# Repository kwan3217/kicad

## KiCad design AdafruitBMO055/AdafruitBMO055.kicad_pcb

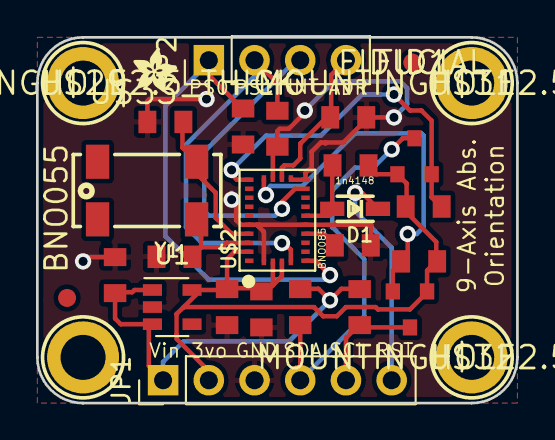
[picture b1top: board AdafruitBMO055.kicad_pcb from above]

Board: 2 copper layers, 26.7 x 20.3 mm, 31 parts (0 on the bottom side), 16 nets.

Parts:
C1, C2: 22pF; SMD_0805
C3, C4: 0.1uF; SMD_0805
C5, C6: 10uF; SMD_0805
D1: 1n4148; SOD-323
FID1, FID2: FIDUCIAL; FIDUCIAL_1MM
JP1: Pin_Header_Straight_1x06_Pitch2.54mm
JP2: Pin_Header_Straight_1x04_Pitch2.54mm
Q1, Q2: BSS138; SOT-23
R3, R4, R5, R6, R7, R8, R9, R10: 10K; SMD_0805
U1: MIC5225; SOT-23-5
U$2: BNO085; BNO055
U$3: PCBFEAT-REV-040
U$28: ADAFRUIT_TEXT_20MM
U$29, U$30, U$31, U$32: MOUNTINGHOLE2.5_THICK; MOUNTINGHOLE_2.5_PLATED_THICK
U$33: ADAFRUIT_2.5MM
Y1: 32.768kHz; CRYSTAL_8X3.8

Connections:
+3V3: C4.2, C6.1, JP1.2, Q1.1, Q2.1, R6.1, R7.1, R10.1, U1.5, U$2.3, U$2.4, U$2.28
+5V: C5.1, JP1.1, R8.1, R9.1, U1.1, U1.3
/I2CADDR_3V: JP2.4, R5.1, U$2.17
/INT_3V: JP2.3, U$2.14
/N$1: C1.2, U$2.27, Y1.1
/N$2: C2.2, U$2.26, Y1.2
/N$3: C3.2, U$2.9
/NRESET_3V: D1.2, R10.2, U$2.11
/PS0_3V: JP2.1, R3.1, U$2.6
/PS1_3V: JP2.2, R4.1, U$2.5
/RST_5V: D1.1, JP1.6
/SCL_3V: Q2.2, R7.2, U$2.19
/SCL_5V: JP1.5, Q2.3, R9.2
/SDA_3V: Q1.2, R6.2, U$2.20
/SDA_5V: JP1.4, Q1.3, R8.2
GND: C1.1, C2.1, C3.1, C4.1, C5.2, C6.2, JP1.3, R3.2, R4.2, R5.2, U1.2, U$2.2, U$2.10, U$2.15, U$2.16, U$2.18, U$2.25

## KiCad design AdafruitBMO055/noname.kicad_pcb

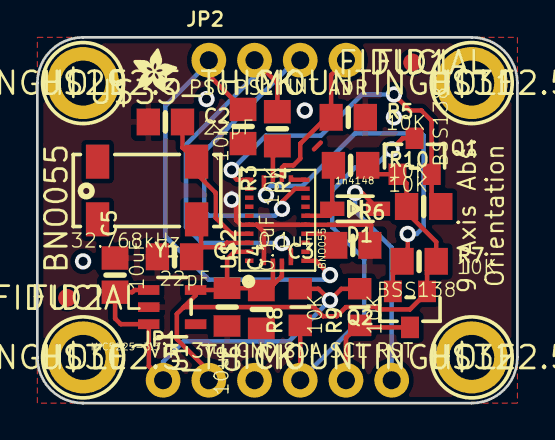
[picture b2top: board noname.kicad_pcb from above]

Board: 2 copper layers, 26.7 x 20.3 mm, 31 parts (0 on the bottom side), 16 nets.

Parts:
C1, C2: 22pF; 0805-NO
C3: 0.1uF; 0805-NO
C4: 0.1uF; 0805_10MGAP
C5: 10uF; 0805-NO
C6: 10uF; 0805_10MGAP
D1: 1n4148; SOD-323
FID1, FID2: FIDUCIAL; FIDUCIAL_1MM
JP1: 1X06_ROUND_76
JP2: 1X04_ROUND_76
Q1, Q2: BSS138; SOT23-WIDE
R3, R4, R5, R6, R7, R10: 10K; 0805-NO
R8, R9: 10K; _0805MP
U1: MIC5225-3.3; SOT23-5
U$2: BNO055
U$3: PCBFEAT-REV-040
U$28: ADAFRUIT_TEXT_20MM
U$29, U$30, U$31, U$32: MOUNTINGHOLE2.5_THICK; MOUNTINGHOLE_2.5_PLATED_THICK
U$33: ADAFRUIT_2.5MM
Y1: 32.768kHz; CRYSTAL_8X3.8

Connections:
3.3V: C4.2, C6.1, JP1.2, Q1.1, Q2.1, R6.2, R7.2, R10.2, U1.5, U$2.3, U$2.4, U$2.28
5.0V: C5.1, JP1.1, R8.2, R9.2, U1.1, U1.3
GND: C1.1, C2.1, C3.1, C4.1, C5.2, C6.2, JP1.3, R3.2, R4.2, R5.2, U1.2, U$2.2, U$2.10, U$2.15, U$2.16, U$2.18, U$2.25
I2CADDR_3V: JP2.4, R5.1, U$2.17
INT_3V: JP2.3, U$2.14
unnamed: C1.2, U$2.27, Y1.P$4
unnamed: C2.2, U$2.26, Y1.P$1
unnamed: C3.2, U$2.9
NRESET_3V: D1.A, R10.1, U$2.11
PS0_3V: JP2.1, R3.1, U$2.6
PS1_3V: JP2.2, R4.1, U$2.5
RST_5V: D1.C, JP1.6
SCL_3V: Q2.2, R7.1, U$2.19
SCL_5V: JP1.5, Q2.3, R9.1
SDA_3V: Q1.2, R6.1, U$2.20
SDA_5V: JP1.4, Q1.3, R8.1

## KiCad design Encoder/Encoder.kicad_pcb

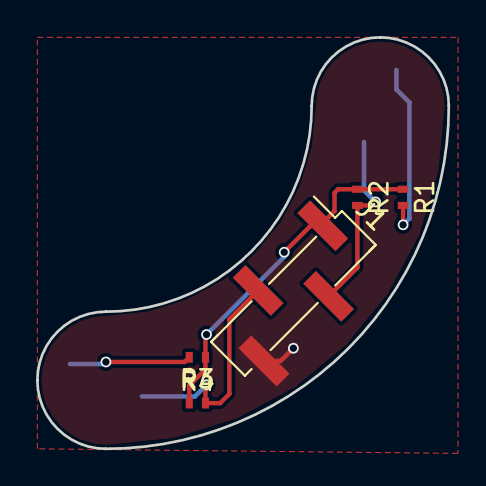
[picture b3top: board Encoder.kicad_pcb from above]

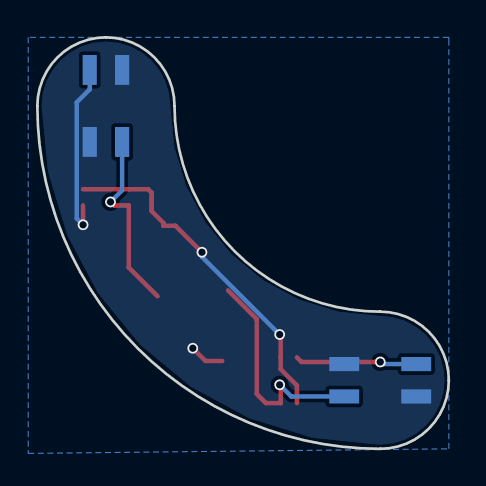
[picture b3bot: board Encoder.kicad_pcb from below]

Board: 2 copper layers, 22.9 x 22.9 mm, 7 parts (2 on the bottom side), 6 nets.

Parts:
J1: CONN_01X04; Pin_Header_Straight_1x04_Pitch2.54mm_SMD_Pin1Left
R1, R3: 220; R_0402_NoSilk
R2, R4: 10k; R_0402_NoSilk
U1, U2: QRE1113

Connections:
/D0: R1.2, U1.1
/D1: R3.2, U2.1
/ENC0: J1.2, R2.2, U1.3
/ENC1: J1.3, R4.2, U2.3
GND: J1.4, U1.2, U1.4, U2.2, U2.4
VCC: J1.1, R1.1, R2.1, R3.1, R4.1

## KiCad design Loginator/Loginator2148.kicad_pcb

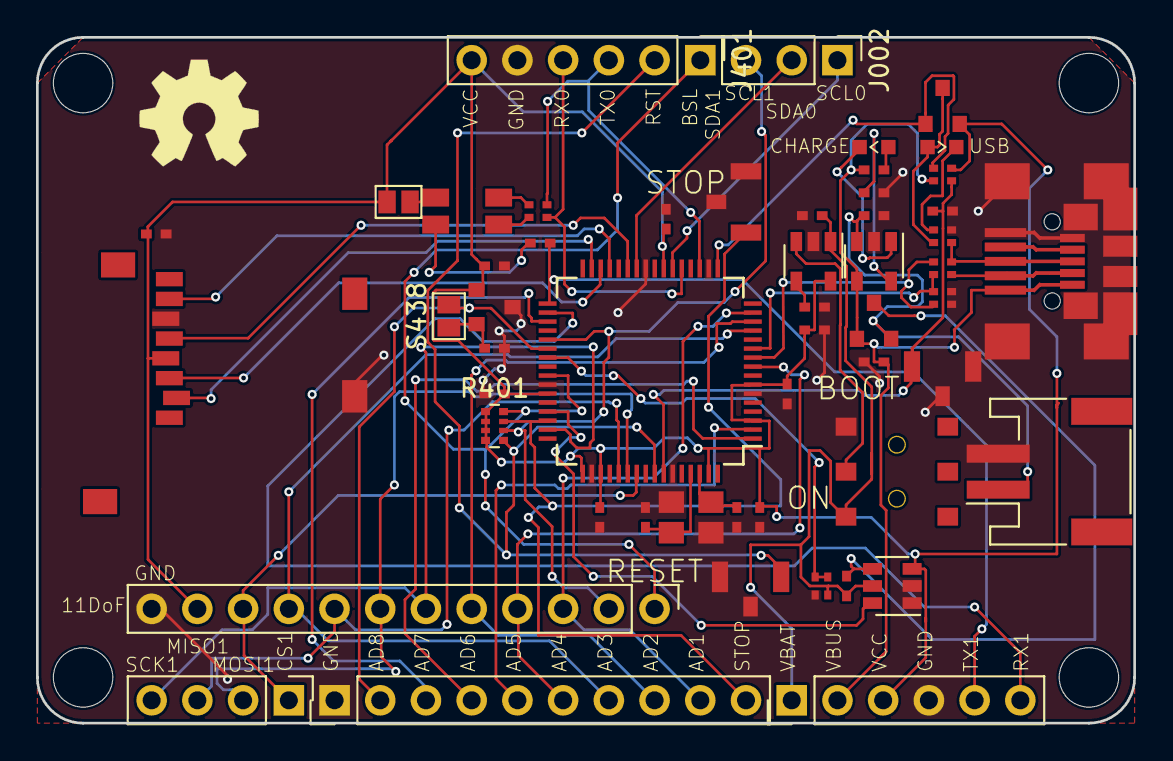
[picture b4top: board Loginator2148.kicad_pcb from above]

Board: 2 copper layers, 61.0 x 38.1 mm, 57 parts (0 on the bottom side), 54 nets.

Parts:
C023: 18pF; R_Array_Convex_2x0402
C201: 1uF; SMD_0402
C204, C407, C423, C432, C443, C451, C463, C701: 100nF; SMD_0402
C205: 4.7nF; SMD_0402
C301, C302, C438: 4.7uF; SMD_0402
C461, C462: 18pF; SMD_0402
D050, D301: RED; D_0603
D302: DCC; SOT-23
D401: HSMF-C118
J001: USB_MICROB; USB_Double-B
J002: M01PTH; Pin_Header_Straight_1x03_Pitch2.54mm
J301: JST 2mm; JST_PH_S2B-PH-SM4-TB_02x2.00mm_Angled
J401, J404: M06; Pin_Header_Straight_1x06_Pitch2.54mm
J402: M04; Pin_Header_Straight_1x04_Pitch2.54mm
J403: M10; Pin_Header_Straight_1x10_Pitch2.54mm
J406: 11DoF; Pin_Header_Straight_1x12_Pitch2.54mm
J701: Micro_SD_Card_Det_Hirose_DM3AT; MICROSD-SOCKET-PP
JP1, JP2, JP3, JP4: STAND-OFF
Q050: PMOS; SOT-23
R011: 22k; SMD_0402
R015: 10k; R_Array_Convex_2x0402
R023, R419: 33; R_Array_Convex_2x0402
R035: 1.5k; R_Array_Convex_2x0402
R201: 100k; R_Array_Convex_2x0402
R203: 0.047; SMD_0402
R301: 10k; SMD_0402
R302: 1.5k; SMD_0402
R401: 10k; R_Array_Convex_4x0402
R433: 150; SMD_0402
S010, S420, S457: SPST; SW_SPST_B3U-1100P
S201: SPDT; SWITCH_DPDT_AZY0202
S401, S438: GS2
U201: 3.3V; SOT-23-5
U202: MAX4173; SOT-23-6
U301: MCP73831; SOT-23-5
U401: LPC2148; LQFP-64_10x10mm_Pitch0.5mm
U402: 1525; SOT-23
Y401: 12MHz; Crystal_SMD_Abracon_ABM8G-4pin_3.2x2.5mm

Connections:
/AD1: J403.9, J406.3, U401.15
/AD2: J403.8, J406.5, U401.14
/AD3: J403.7, J406.9, U401.13
/AD4: J403.6, J406.4, U401.9
/AD5: J403.5, U401.2
/AD6: J403.4, U401.1
/AD7: J403.3, U401.35
/ADREF+: C438.1, S438.1, U402.2
/ADREF-: J403.2, S438.2, U401.38
/BATLVL: R201.3, R201.4, U401.39
/C+LED-: D301.1, U301.1
/CONN_D+: J001.3, R023.4, R035.1
/CONN_D-: J001.2, R023.3
/CS0: J701.2, U401.31
/CS1: J402.1, J406.10, U401.55
/CURRENT: U202.6, U401.45
/C_LED+: D301.2, R302.2
/DB: D401.4, R419.1
/DG: D401.3, R419.2
/DR: D401.2, R433.2
/MISO0: J701.7, U401.29
/MISO1: J402.3, J406.8, U401.53
/MOSI0: J701.3, U401.30
/MOSI1: J402.2, J406.7, U401.54
/PROG: R301.2, U301.5
/RGB_Q: D401.1, S401.2
/RST: J401.2, R401.5, S457.2, U401.57
/RX0(PWMG): J401.4, R419.3, U401.21
/RX1: J404.6, U401.34
/SCK0: J701.5, U401.27
/SCK1: J402.4, J406.6, U401.47
/SCL0: J002.1, U401.22
/SCL1: J002.3, J406.2, R401.6, U401.37
/SDA0: J002.2, U401.26
/SDA1(BSL): J401.1, J406.1, R401.8, U401.41
/STOP: J403.10, R401.7, S420.2, U401.46
/Sheet59FCEA5F/BYP: C204.1, U201.4
/Sheet59FCEA5F/PWR_EN: S201.2, U201.3
/TX0(PWMB): J401.3, R419.4, U401.19
/TX1(PWMR): J404.5, R433.1, U401.33
/UC_LED+: D050.2, Q050.3, R035.4
/UC_LED-: D050.1, R035.3
/USBD+: C023.2, R023.1, U401.10
/USBD-: C023.1, R023.2, U401.11
/USB_ON: R011.2, R015.1, S010.1, U401.58
/USB_SOFTCONNECT: Q050.1, R015.3, U401.17
/VBUS: C302.1, D302.1, J001.1, J404.2, R015.4, R302.1, U301.4
/VIN+: D302.3, R203.1, U202.4
/VIN-: C201.1, J404.1, R201.2, R203.2, S201.1, U201.1, U202.5
/VLIPO: C301.1, D302.2, J301.1, U301.3
/XTAL1: C462.2, U401.62, Y401.1
/XTAL2: C461.2, U401.61, Y401.3
GND: C023.3, C023.4, C201.2, C204.2, C205.2, C301.2, C302.2, C407.2, C423.2, C432.2, C438.2, C443.2, C451.2, C461.1, C462.1, C463.2, C701.2, J001.5, J001.6, J301.2, J401.5, J403.1, J404.4, J406.12, J701.6, J701.9, R011.1, R035.2, R201.1, R301.1, S010.2, S010.3, S201.3, S420.1, S420.3, S457.1, S457.3, U201.2, U202.1, U202.2, U301.2, U401.6, U401.18, U401.25, U401.42, U401.50, U401.59, U402.3, Y401.2, Y401.4
VCC: C205.1, C407.1, C423.1, C432.1, C443.1, C451.1, C463.1, C701.1, J401.6, J404.3, J406.11, J701.4, Q050.2, R015.2, R401.1, R401.2, R401.3, R401.4, S401.1, U201.5, U202.3, U401.3, U401.7, U401.23, U401.43, U401.49, U401.51, U401.63, U402.1

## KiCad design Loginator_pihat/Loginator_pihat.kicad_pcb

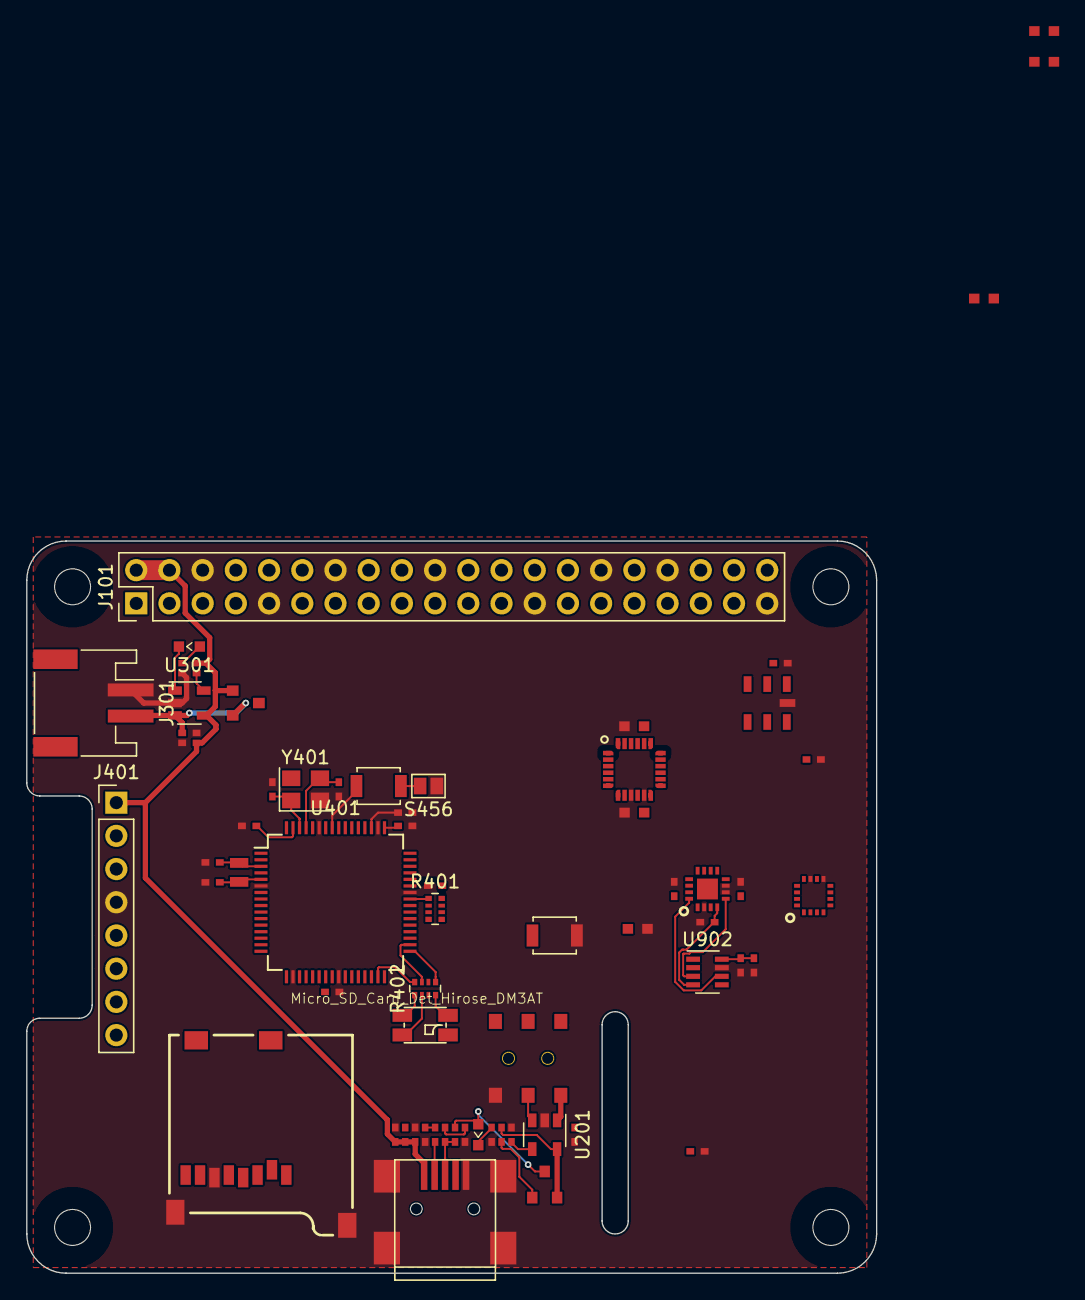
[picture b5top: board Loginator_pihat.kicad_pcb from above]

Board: 2 copper layers, 65.0 x 56.0 mm, 65 parts (0 on the bottom side), 49 nets.

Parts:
C010, C204, C423: 1uF; SMD_0402
C020, C030: 22pF; SMD_0402
C101, C214, C443, C449, C451, C463, C904, C905, C907, C916: 100nF; SMD_0402
C215: 4.7nF; SMD_0402
C301, C302, C914: 4.7uF; SMD_0402
C403, C405: 18pF; SMD_0402
C461, C462: 33pF; SMD_0402
C610, C613, C802: 100nF; SMD_0603
C620: 2.2nF; SMD_0603
C808: 220nF; SMD_0603
C810: 4.7uF; SMD_0603
C908: 10uF; SMD_0402
D050: BLUE; D_0603
D301: YELLOW; D_0603
D302: DCC; SOT-23
D401: HSMF-C118
J001: USB_MICROB; USB_Mini-B
J101: Raspberry_Pi_40; Pin_Header_Straight_2x20_Pitch2.54mm
J301: JST 2mm; JST_PH_S2B-PH-SM4-TB_02x2.00mm_Angled
J401: M07; Pin_Header_Straight_1x08_Pitch2.54mm
J701: Micro_SD_Card_Det_Hirose_DM3AT; MICROSD-SOCKET-PP
Q050: PMOS; SOT-23
R010, R051, R301: 10k; SMD_0402
R011: 100k; SMD_0402
R020, R030: 33; SMD_0402
R031, R050, R302: 1.5k; SMD_0402
R401: 10k; R_Array_Convex_4x0402
R402: 1.5k; R_Array_Convex_4x0402
S201: SPDT; SWITCH_DPDT_AZY0202
S456: SOLDERJUMPERNO; GS2
S457: SPST; SW_SPST_B3U-1000P
S458: B3U-1000P; SW_SPST_B3U-1000P
U101: BMP180
U201: 3.3V; SOT-23-5
U301: MCP73831; SOT-23-5
U401: LPC2148; LQFP-64_10x10mm_Pitch0.5mm
U601: MPU6050; MPU60x0
U801: HMC5883L
U901: ADXL377
U902: AD7991; SOT-23-8
Y401: 12MHz; Crystal_SMD_Abracon_ABM8G-4pin_3.2x2.5mm
Y402: 32kiHz; ABS06

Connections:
/ACCINT: U401.47, U601.12
/BSL: J401.5, R401.1, U401.41
/BYP: C214.1, U201.4
/COMPINT: U401.35, U801.15
/CONN_D+: J001.3, R030.1, R031.1
/CONN_D-: J001.2, R020.1
/CS0: J701.2, U401.45
/DB: D401.4, R402.2
/DG: D401.3, R402.1
/DR: D401.2, R402.4
/HMC5883L/C1: C810.2, U801.10
/HMC5883L/SETC: C808.2, U801.12
/HMC5883L/SETP: C808.1, U801.8
/HighAcc/XACC: C905.2, U901.5, U902.3
/HighAcc/YACC: C904.2, U901.4, U902.4
/HighAcc/ZACC: C916.2, U901.16, U902.6
/MISO0: J701.7, U401.29
/MOSI0: J701.3, U401.30
/MPU6050/N$1: C620.1, U601.20
/MPU6050/N$13: C610.2, U601.10
/PROG: R301.2, U301.5
/PWMB: R402.7, U401.34
/PWMG: R402.8, U401.31
/PWMR: R402.5, U401.33
/PWR_EN: S201.2, U201.3
/RST: R401.2, S457.2, U401.57
/RST-: S456.2, S457.1
/RTXC1: C403.2, U401.3, Y402.1
/RTXC2: C405.2, U401.5, Y402.2
/RX0: J401.3, U401.21
/SCK0: J701.5, U401.27
/SCL0: J401.6, R401.4, U101.5, U401.22, U601.23, U801.1, U902.1
/SDA0: J401.7, R401.3, U101.6, U401.26, U601.24, U801.16, U902.2
/STAT+: D301.2, R302.2
/STAT-: D301.1, U301.1
/TX0: J401.2, U401.19
/USBD+: C030.1, R030.2, U401.10
/USBD-: C020.1, R020.2, U401.11
/USB_LIGHT: Q050.1, R051.1, U401.17
/USB_LIGHT+: D050.2, Q050.3, R031.2
/USB_LIGHT-: D050.1, R050.2
/USB_ON: R010.2, S458.1, U401.58
/VBUS: C010.1, C302.1, D302.1, J001.1, J101.2, J101.4, J401.1, R010.1, R011.2, R302.1, U301.4
/VIN+: C204.1, D302.3, S201.1, U201.1
/VLIPO: C301.1, C449.2, D302.2, J301.2, U301.3, U401.49
/XTAL1: C462.2, U401.62, Y401.1
/XTAL2: C461.2, U401.61, Y401.3
GND: C010.2, C020.2, C030.2, C101.1, C204.2, C214.2, C215.2, C301.2, C302.2, C403.1, C405.1, C423.2, C443.2, C449.1, C451.2, C461.1, C462.1, C463.2, C610.1, C613.2, C620.2, C802.1, C810.1, C904.1, C905.1, C907.2, C908.2, C914.2, C916.1, J001.5, J001.6, J101.6, J101.9, J101.14, J101.20, J101.25, J101.30, J101.34, J101.39, J301.1, J401.4, J701.6, J701.9, R011.1, R050.1, R301.1, S201.3, S456.1, S458.2, U101.7, U201.2, U301.2, U401.6, U401.18, U401.25, U401.42, U401.50, U401.59, U601.1, U601.9, U601.11, U601.18, U801.9, U801.11, U901.2, U901.6, U901.7, U902.7, Y401.2
VCC: C101.2, C215.1, C423.1, C443.1, C451.1, C463.1, C613.1, C802.2, C907.1, C908.1, C914.1, D401.1, J401.8, J701.4, Q050.2, R051.2, R401.5, R401.6, R401.7, R401.8, U101.2, U101.3, U201.5, U401.7, U401.23, U401.43, U401.51, U401.63, U601.8, U601.13, U801.2, U801.4, U801.13, U901.14, U901.15, U902.8

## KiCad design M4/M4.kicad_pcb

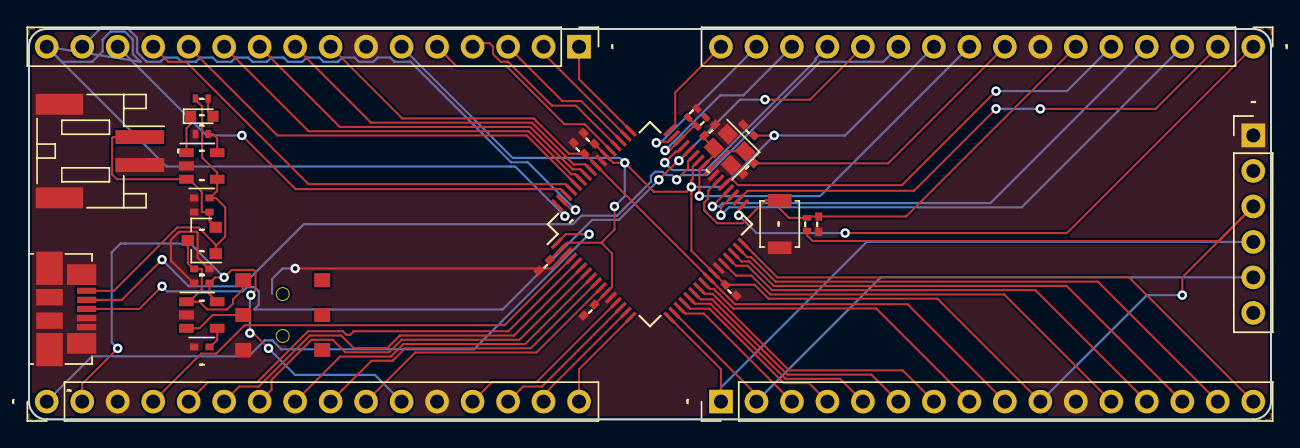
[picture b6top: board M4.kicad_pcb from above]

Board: 2 copper layers, 88.9 x 27.9 mm, 35 parts (1 on the bottom side), 63 nets.

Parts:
C201, C205, C303, C304: 4.7uF; C_0402_NoSilk
C204, C402, C411, C426, C438, C442, C454: 100nF; C_0402_NoSilk
C440, C441: 22pF; C_0402_NoSilk
C456: 3.3uF; C_0402_NoSilk
D301: Yellow; LED_0603
D302: PMEG2005CT; SOT-23
J001: USB_OTG; USB_Micro-B_Molex_47346-0001
J301: Battery_Cell; JST_PH_S2B-PH-SM4-TB_02x2.00mm_Angled
J401, J402, J403, J404: CONN_01X16; Pin_Header_Straight_1x16_Pitch2.54mm
J405: CONN_01X06; Pin_Header_Straight_1x06_Pitch2.54mm
J701: Micro_SD_Card_SPI; MICROSD-SOCKET-PP
R304, R305, R438, R446: 10k; R_0402_NoSilk
R447: 22k; R_0402_NoSilk
S203: SW_DPDT_x2; SWITCH_DPDT_AZY0202
S438: SW_Push; SW_SPST_B3U-1000P
U201: MIC5319-3.3; SOT-23-5
U301: MCP73831; SOT-23-5
U401: TM4C1232; LQFP-64_10x10mm_Pitch0.5mm
Y440: 25MHz; Crystal_SMD_2520-4pin_2.5x2.0mm

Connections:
+3V3: C205.1, C402.1, C411.1, C426.1, C442.1, C454.1, J401.2, J401.11, J402.10, J403.10, J404.6, J405.3, J701.4, R438.1, U201.5, U401.2, U401.11, U401.26, U401.42, U401.54
/1: J401.1, U401.1
/4: J401.4, U401.4
/5: J401.5, U401.5
/6: J401.6, U401.6
/7: J401.7, U401.7
/8: J401.8, U401.8
/9: J401.9, U401.9
/10: J401.10, U401.10
/13: J401.13, U401.13
/14: J401.14, U401.14
/15: J401.15, U401.15
/16: J401.16, U401.16
/23: J402.7, U401.23
/24: J402.8, U401.24
/28: J402.12, U401.28
/29: J402.13, U401.29
/30: J402.14, U401.30
/31: J402.15, U401.31
/32: J402.16, U401.32
/33: J403.1, U401.33
/34: J403.2, U401.34
/35: J403.3, U401.35
/36: J403.4, U401.36
/37: J403.5, U401.37
/45: J403.13, U401.45
/47: J403.15, U401.47
/48: J403.16, U401.48
/49: J404.1, U401.49
/50: J404.2, U401.50
/51: J404.3, U401.51
/52: J404.4, U401.52
/53: J404.5, U401.53
/57: J404.9, U401.57
/58: J404.10, U401.58
/59: J404.11, U401.59
/60: J404.12, U401.60
/61: J404.13, U401.61
/62: J404.14, U401.62
/63: J404.15, U401.63
/64: J404.16, U401.64
/BYPASS: C204.1, U201.4
/CS_SD: J402.4, J701.2, U401.20
/D+: J001.3, J403.12, U401.44
/D-: J001.2, J403.11, U401.43
/ENABLE: S203.2, U201.3
/MISO0: J402.5, J701.7, U401.21
/MOSI0: J402.6, J701.3, U401.22
/OSC0: C440.2, J403.8, U401.40, Y440.1
/OSC1: C441.2, J403.9, U401.41, Y440.3
/PROG: R305.1, U301.5
/RESET: C438.2, J403.6, R438.2, S438.2, U401.38
/RX0: J402.1, J405.4, U401.17
/SCK0: J402.3, J701.5, U401.19
/STAT+: D301.2, R304.1
/STAT-: D301.1, U301.1
/TX0: J402.2, J405.5, U401.18
/VBUS+: C304.2, D302.1, J001.1, R304.2, R446.1, U301.4
/VBUS-: J403.14, R446.2, R447.1, U401.46
/VDDC: C456.1, J402.9, J404.8, U401.25, U401.56
/VIN: C201.1, D302.3, S203.3, U201.1
/VLIPO: C303.1, D302.2, J301.1, U301.3
GND: C201.2, C204.2, C205.2, C303.2, C304.1, C402.2, C411.2, C426.2, C438.1, C440.1, C441.1, C442.2, C454.2, C456.2, J001.4, J001.5, J001.6, J301.2, J401.3, J401.12, J402.11, J403.7, J404.7, J405.1, J701.6, J701.9, R305.2, R447.2, S203.1, S438.1, U201.2, U301.2, U401.3, U401.12, U401.27, U401.39, U401.55, Y440.2, Y440.4

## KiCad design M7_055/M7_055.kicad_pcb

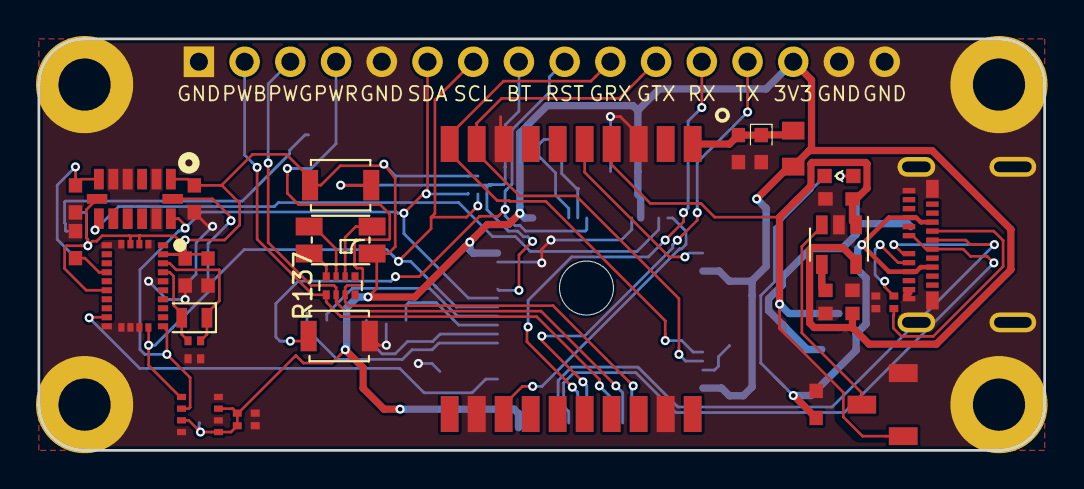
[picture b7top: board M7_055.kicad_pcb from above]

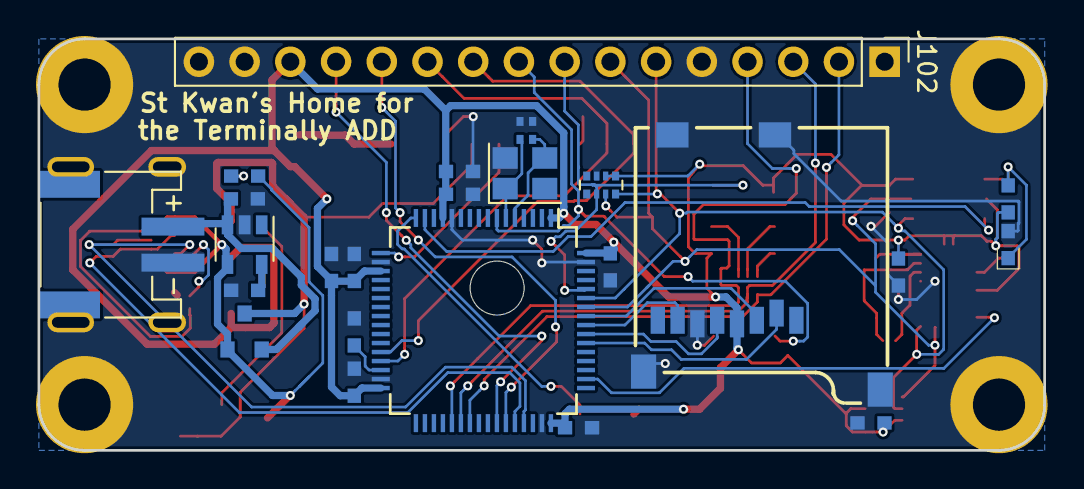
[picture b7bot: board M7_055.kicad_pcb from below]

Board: 2 copper layers, 55.9 x 22.9 mm, 56 parts (24 on the bottom side), 44 nets.

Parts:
B601: JST 2mm; SPARKFUN_JST_POWER
C105, C226: 22pF; R_Array_Convex_2x0402
C112, C701: 1uF; SMD_0603
C113: 10nF; SMD_0603
C118, C130, C602, C603, C705: 4.7uF; SMD_0603
C119, C132, C148, C164, C203, C209, C301, C501, C505, C704, C801: 100nF; SMD_0603
C225: 120nF; SMD_0603
C228: 6.8nF; SMD_0603
C303, C506: 10uF; SMD_0603_pol
C406: 100nF; R_Array_Convex_2x0402
D137: HSMF-C118
D601: YELLOW; D_0603
D602: DCC; SOT-23
J101: USB_C2; MolexUSBTypeC2
J102: Conn_01x16; Pin_Header_Straight_1x16_Pitch2.54mm
J103, J104, J105, J106: STANDOFF_GND; MountingHole_2.9mm_M2.5_Pad
J801: Micro_SD_Card_Det_Hirose_DM3AT; MICROSD-SOCKET-PP
L301: Ferrite; SMD_0805
R107: 10k; R_Array_Convex_4x0402
R137: 68; R_Array_Convex_4x0402
R174: 5.1k; R_Array_Convex_2x0402
R506: 100; SMD_0603
R601: 10k; SMD_0603
R604: 1.5k; SMD_0603
S107, S160: SW_SPST; SW_SPST_B3U-1000P
S701: SPDT; SW_SPST_CJS120xA
U101: STM32F722; LQFP-64_10x10mm_Pitch0.5mm
U201: BNO055
U301: FGPMMOPA6H
U401: BME280
U501: ADXL375
U601: MCP73831; SOT-23-5
U701: 3.3V; SOT-23-5
Y101: 12MHz; Crystal_SMD_3225-4pin_3.2x2.5mm
Y201: 32kiHz; Crystal_SMD_2012-2pin_2.0x1.2mm

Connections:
+3V3: C112.2, C113.2, C118.2, C119.2, C132.2, C148.2, C164.2, C203.2, C225.1, C228.1, C406.1, C406.2, C501.1, C705.1, C801.1, D137.1, J102.14, J801.4, L301.1, R107.5, R107.6, R506.1, S160.1, U101.1, U101.13, U101.19, U101.32, U101.48, U101.64, U201.3, U201.4, U201.11, U201.28, U401.2, U401.6, U401.8, U501.1, U501.7, U701.5
/ADXL_INT: U101.15, U501.8
/BNO055/CAP: C209.1, U201.9
/BNO055/XIN32: C226.1, U201.27, Y201.1
/BNO055/XOUT32: C226.2, U201.26, Y201.2
/BNO_INT: U101.50, U201.14
/BOOT: J102.8, R107.2, S160.2, U101.60
/CC1: J101.7, R174.2
/CC2: J101.4, R174.1
/CS_uSD: J801.2, U101.54
/D+: J101.3, U101.45
/D-: J101.2, U101.44
/GPS/VGPS: C301.2, C303.1, L301.2, U301.1
/GPS_FIX: U101.17, U301.5
/GPS_PPS: U101.16, U301.13
/GPS_RX: J102.10, U101.28, U301.10
/GPS_TX: J102.11, U101.29, U301.9
/HighAcc/VS: C505.1, C506.1, R506.2, U501.6
/M7_RX: J102.12, U101.43
/M7_TX: J102.13, U101.42
/MISO: J801.7, U101.56
/MOSI: J801.3, U101.57
/PWMB: J102.2, R137.1, U101.39
/PWMB-: D137.4, R137.8
/PWMG: J102.3, R137.2, U101.38
/PWMG-: D137.3, R137.7
/PWMR: J102.4, R137.3, U101.37
/PWMR-: D137.2, R137.6
/RESET: J102.9, S107.1, U101.7
/Regulator/BYP: C704.1, U701.4
/Regulator/PWR_EN: S701.2, U701.3
/SCK: J801.5, U101.55
/SCL: J102.7, R107.3, U101.58, U201.19, U401.4, U501.14
/SDA: J102.6, R107.4, U101.59, U201.20, U401.3, U501.13
/Sheet5A4D5668/PROG: R601.2, U601.5
/Sheet5A4D5668/STAT+: D601.2, R604.2
/Sheet5A4D5668/STAT-: D601.1, U601.1
/Sheet5A4D5668/VLIPO: B601.+, C603.1, D602.2, U601.3
/VBUS: C602.1, D602.1, J101.1, R604.1, U601.4
/VCAP: C130.2, U101.30
/VRAW: C701.1, D602.3, S701.1, U301.4, U701.1
/XIN: C105.2, U101.5, Y101.3
/XOUT: C105.1, U101.6, Y101.1
GND: B601.-, C105.3, C105.4, C112.1, C113.1, C118.1, C119.1, C130.1, C132.1, C148.1, C164.1, C203.1, C209.2, C225.2, C226.3, C226.4, C228.2, C301.1, C303.2, C406.3, C406.4, C501.2, C505.2, C506.2, C602.2, C603.2, C701.2, C704.2, C705.2, C801.2, J101.5, J101.6, J102.1, J102.5, J102.15, J102.16, J103.1, J104.1, J105.1, J106.1, J801.6, J801.9, J801.10, R107.7, R174.3, R174.4, R601.1, S107.2, S701.3, U101.12, U101.18, U101.31, U101.47, U101.63, U201.2, U201.5, U201.6, U201.15, U201.16, U201.17, U201.18, U201.25, U301.3, U301.8, U301.12, U301.19, U401.1, U401.5, U401.7, U501.2, U501.4, U501.5, U501.12, U601.2, U701.2, Y101.4

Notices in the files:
Loginator/Loginator2148.kicad_pcb:
Released under the Creative Commons Attribution Share-Alike 3.0 License
http://creativecommons.org/licenses/by-sa/3.0
